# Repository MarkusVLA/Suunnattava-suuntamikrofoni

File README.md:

# Suunnattava suuntamikrofoni 

Suunnattava suuntamikrofoni on laite, jolla voidaan elektronisesti ohjata äänityksen suuntaa käännettävän suuntauksen avulla. Laite koostuu kahdesta piirikortista: Ensimmäinen piirikortti sisältää kuuden mikrofonin ryhmän, josta luetaan dataa. Toinen piirikortti hoitaa signaalinkäsittelyn ja laitteen ohjauksen ESP32-S3-mikro-ohjaimeen perustuvalla järjestelmällä.

## Mikrofonipiiri

-   ...

## Signaalinkäsittelypiiri

<p float="left">

  <p>Kuva 1: ESP32-DSP piirikaavio ja piirikortti</p>
</p>

<p float="left">
  
  <p>Kuva 2: ESP32-DSP piirikortti toteutettuna</p>
</p>

## TODO
* [x] DSP alustan suunnittelu
* [x] Mikrofoonipiirin suunnittelu
* [x] Piirikorttien kasaus
* [x] Datan keräys ADS8688-ADC:n avulla
* [ ] Beam forming algoritmi
* [ ] Äänen toisto käyttäjälle

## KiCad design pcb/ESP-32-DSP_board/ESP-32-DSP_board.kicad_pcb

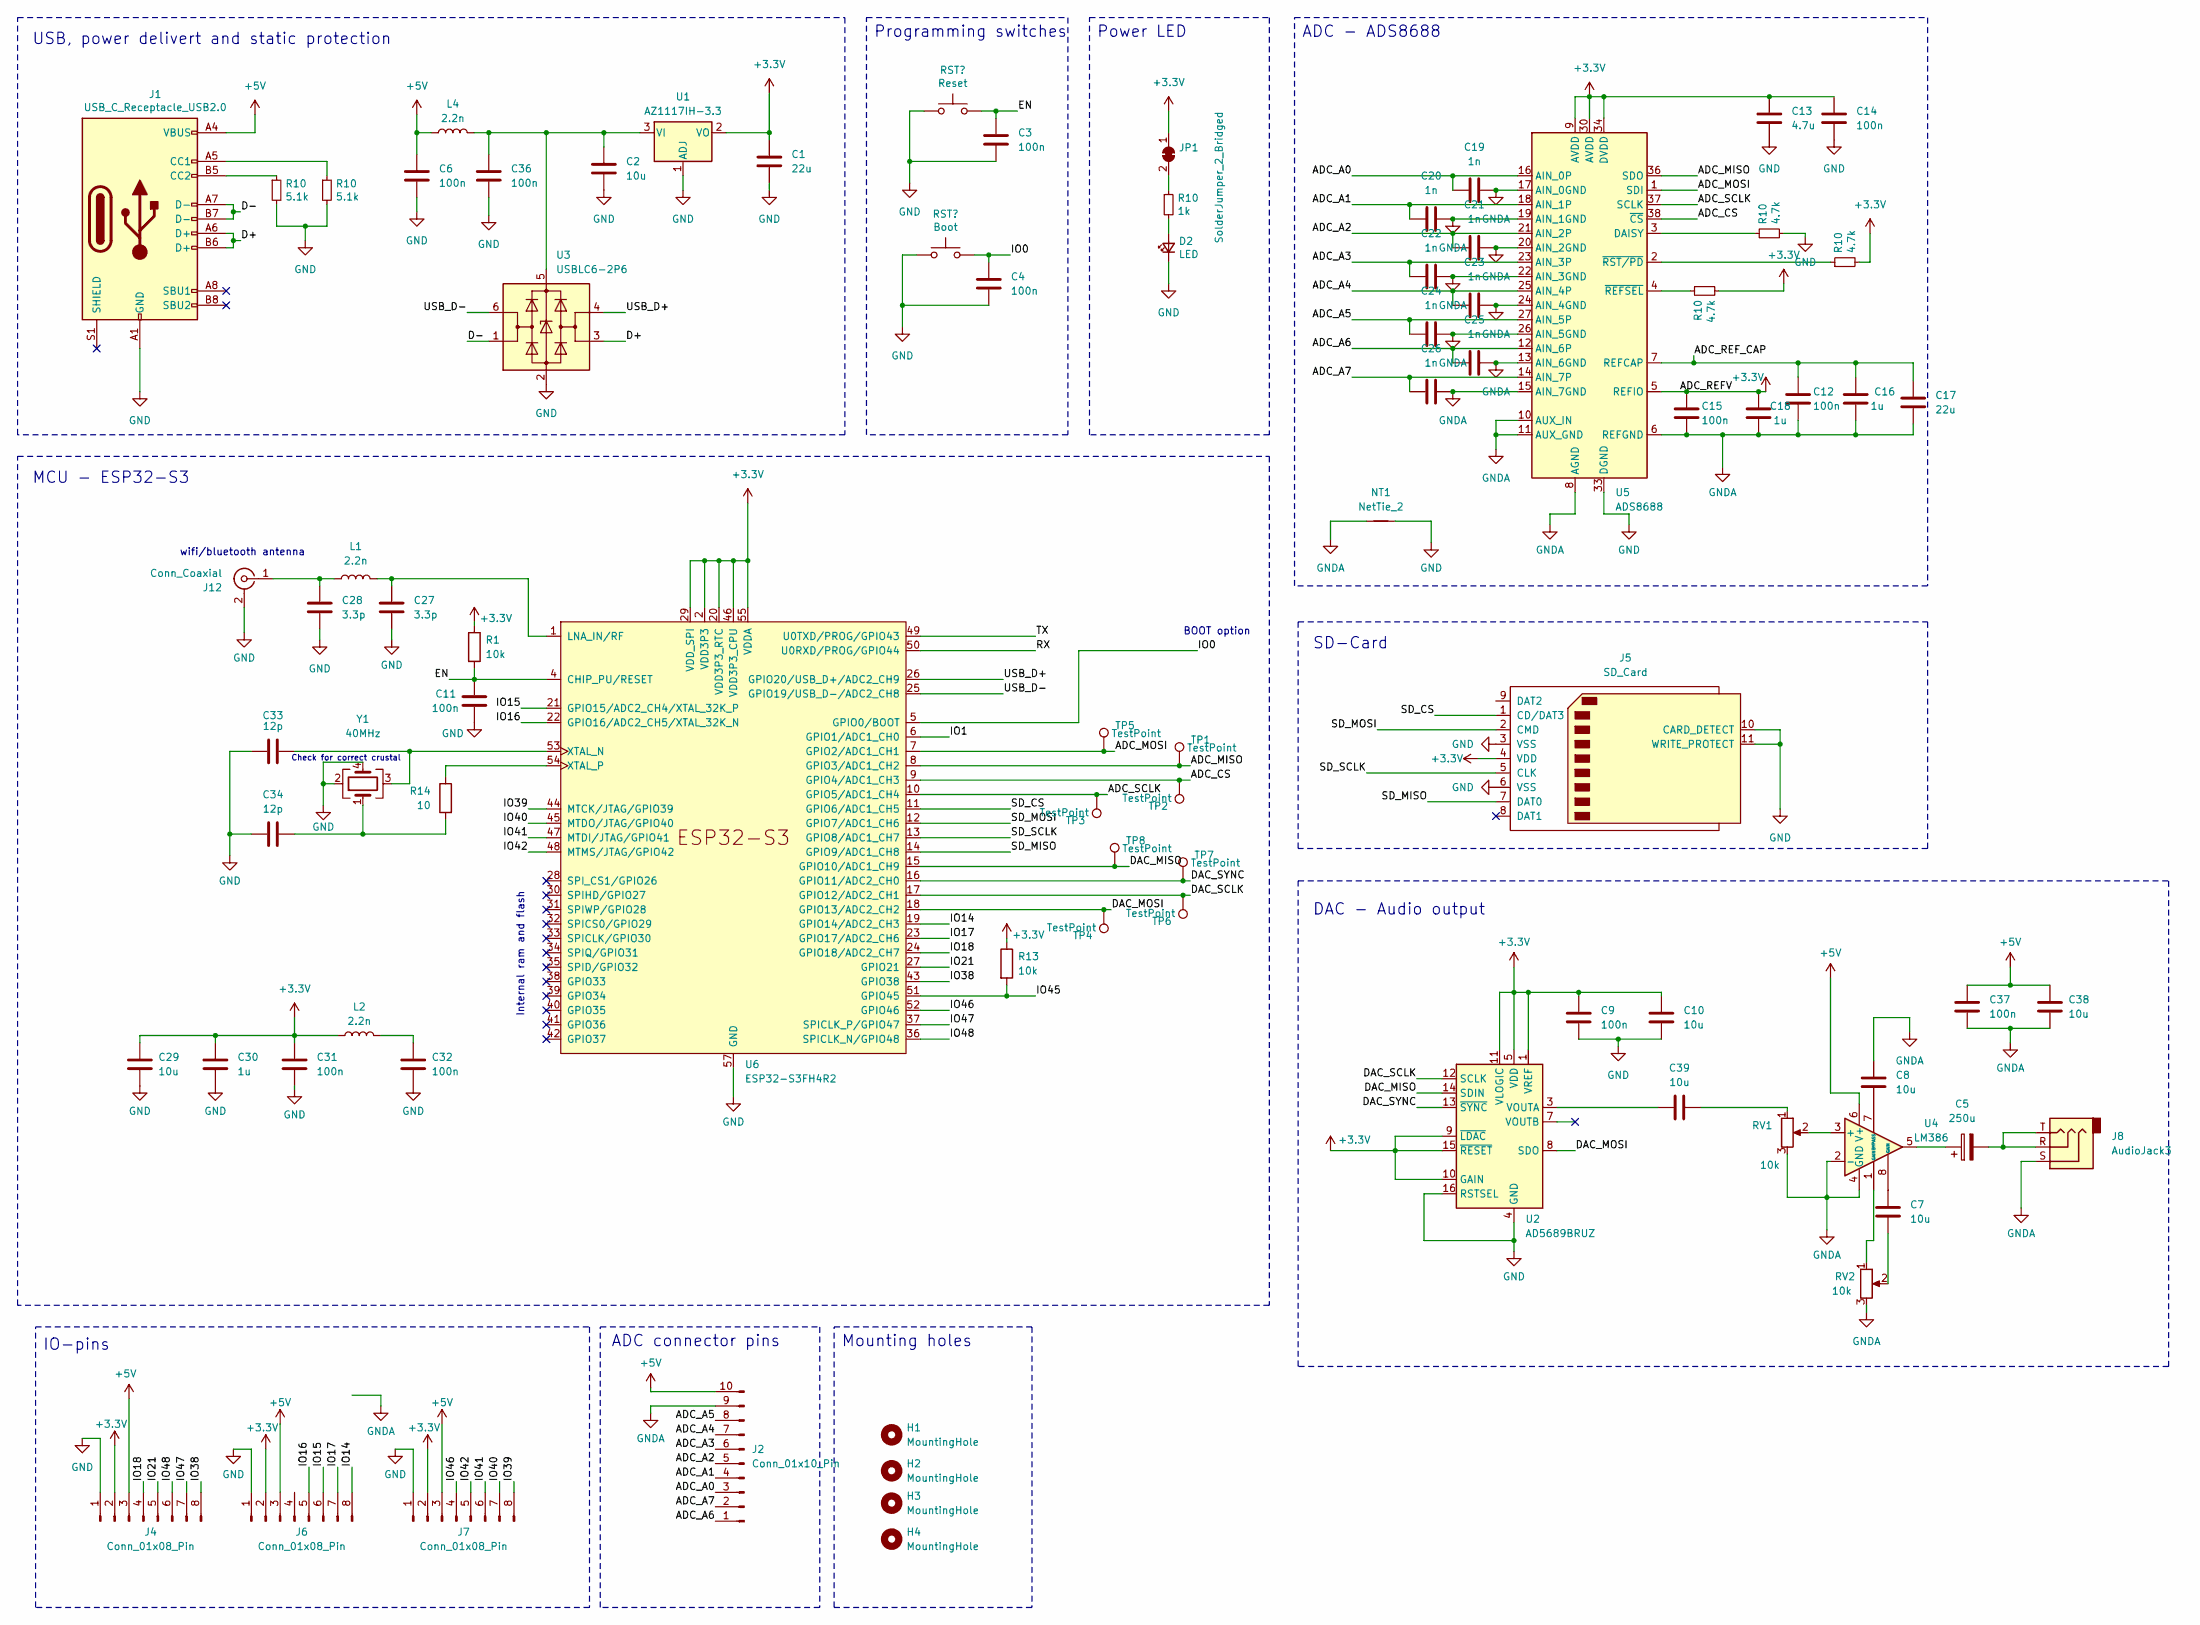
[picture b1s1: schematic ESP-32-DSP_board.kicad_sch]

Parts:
C1, C17: 22u; C_0805_2012Metric
C2, C7, C8, C10, C29, C38, C39: 10u; C_0603_1608Metric
C3, C4, C6, C9, C11, C12, C14, C15, C31, C32, C36, C37: 100n; C_0402_1005Metric
C5: 250u; CP_Radial_D5.0mm_P2.50mm
C13: 4.7u; C_0603_1608Metric
C16, C18, C30: 1u; C_0603_1608Metric
C19, C20, C21, C22, C23, C24, C25, C26: 1n; C_0402_1005Metric
C27, C28: 3.3p; C_0402_1005Metric
C33, C34: 12p; C_0402_1005Metric
D2: LED; LED_0805_2012Metric_Pad1.15x1.40mm_HandSolder; LCSC C205445
H1, H2, H3, H4: MountingHole; MountingHole_2.2mm_M2_DIN965_Pad
J1: USB_C_Receptacle_USB2.0; USB_C_Receptacle_G-Switch_GT-USB-7010ASV
J2: Conn_01x10_Pin; PinHeader_1x10_P2.54mm_Vertical
J4, J6, J7: Conn_01x08_Pin; PinHeader_1x08_P2.54mm_Vertical
J5: SD_Card; microSD_HC_Hirose_DM3D-SF
J8: AudioJack3; Jack_3.5mm_CUI_SJ-3523-SMT_Horizontal
J12: Conn_Coaxial; Texas_SWRA117D_2.4GHz_Right
JP1: SolderJumper_2_Bridged; SolderJumper-2_P1.3mm_Bridged_RoundedPad1.0x1.5mm
L1, L2, L4: 2.2n; L_0603_1608Metric
NT1: NetTie_2; NetTie-2_THT_Pad1.0mm
R1, R13: 10k; R_0402_1005Metric
R10: 4.7k; R_0402_1005Metric; LCSC C163928
R14: 10; R_0805_2012Metric
RV1, RV2: 10k; Potentiometer_Bourns_3214J_Horizontal
SW1: Reset; SW_Push_SPST_NO_Alps_SKRK; LCSC C115357
TP1, TP2, TP3, TP4, TP5, TP6, TP7, TP8: TestPoint; TestPoint_Pad_D1.0mm
U1: AZ1117IH-3.3; SOT-223-3_TabPin2
U2: AD5689BRUZ; TSSOP-16_4.4x5mm_P0.65mm
U3: USBLC6-2P6; SOT-666
U4: LM386; SOIC-8_3.9x4.9mm_P1.27mm
U5: ADS8688; TSSOP-38_4.4x9.7mm_P0.5mm; JLCPCB Rotation Offset -90
U6: ESP32-S3FH4R2; QFN-56-1EP_7x7mm_P0.4mm_EP5.6x5.6mm
Y1: 40MHz; Crystal_SMD_3225-4Pin_3.2x2.5mm

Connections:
+3.3V: C1.1, C9.1, C10.1, C13.1, C14.1, C15.2, C18.1, C29.1, C30.1, C31.1, J4.2, J5.4 (VDD), J6.2, J7.2, JP1.1 (A), L2.1, R1.1, R13.1, U1.2 (VO), U2.1 (VREF), U2.5 (VDD), U2.9 (~LDAC), U2.10 (GAIN), U2.11 (VLOGIC), U2.15 (~RESET), U5.5 (REFIO), U5.9 (AVDD), U5.30 (AVDD), U5.34 (DVDD), U6.2 (VDD3P3), U6.3 (VDD3P3), U6.20 (VDD3P3_RTC), U6.29 (VDD_SPI), U6.46 (VDD3P3_CPU), U6.55 (VDDA), U6.56 (VDDA); also elsewhere on the board
+5V: C6.1, C37.1, C38.1, J1.A4 (VBUS), J1.A9 (VBUS), J1.B4 (VBUS), J1.B9 (VBUS), J2.10, J4.3, J6.3, J7.3, L4.1, U4.6 (V+)
/ADC_A0: C19.1, J2.3, U5.16 (AIN_0P)
/ADC_A1: C20.1, J2.4, U5.18 (AIN_1P)
/ADC_A2: C21.2, J2.5, U5.21 (AIN_2P)
/ADC_A3: C22.2, J2.6, U5.23 (AIN_3P)
/ADC_A4: C23.2, J2.7, U5.25 (AIN_4P)
/ADC_A5: C24.2, J2.8, U5.27 (AIN_5P)
/ADC_A6: C25.1, J2.1, U5.12 (AIN_6P)
/ADC_A7: C26.2, J2.2, U5.14 (AIN_7P)
/ADC_CS: TP2.1, U5.38 (~CS), U6.9 (GPIO4/ADC1_CH3)
/ADC_MISO: TP1.1, U5.36 (SDO), U6.8 (GPIO3/ADC1_CH2)
/ADC_MOSI: TP5.1, U5.1 (SDI), U6.7 (GPIO2/ADC1_CH1)
/ADC_REF_CAP: C12.2, C16.1, C17.1, U5.7 (REFCAP)
/ADC_SCLK: TP3.1, U5.37 (SCLK), U6.10 (GPIO5/ADC1_CH4)
/D+: J1.A6 (D+), J1.B6 (D+), U3.3 (I/O2)
/D-: J1.A7 (D-), J1.B7 (D-), U3.1 (I/O1)
/DAC_MISO: TP8.1, U2.14 (SDIN), U6.15 (GPIO10/ADC1_CH9)
/DAC_MOSI: TP4.1, U2.8 (SDO), U6.18 (GPIO13/ADC2_CH2)
/DAC_SCLK: TP6.1, U2.12 (SCLK), U6.17 (GPIO12/ADC2_CH1)
/DAC_SYNC: TP7.1, U2.13 (~SYNC), U6.16 (GPIO11/ADC2_CH0)
/IO1: U6.6 (GPIO1/ADC1_CH0)
/IO14: J6.8, U6.19 (GPIO14/ADC2_CH3)
/IO15: J6.6, U6.21 (GPIO15/ADC2_CH4/XTAL_32K_P)
/IO16: J6.5, U6.22 (GPIO16/ADC2_CH5/XTAL_32K_N)
/IO17: J6.7, U6.23 (GPIO17/ADC2_CH6)
/IO18: J4.4, U6.24 (GPIO18/ADC2_CH7)
/IO21: J4.5, U6.27 (GPIO21)
/IO38: J4.8, U6.43 (GPIO38)
/IO39: J7.8, U6.44 (MTCK/JTAG/GPIO39)
/IO40: J7.7, U6.45 (MTDO/JTAG/GPIO40)
/IO41: J7.6, U6.47 (MTDI/JTAG/GPIO41)
/IO42: J7.5, U6.48 (MTMS/JTAG/GPIO42)
/IO45: R13.2, U6.51 (GPIO45)
/IO46: J7.4, U6.52 (GPIO46)
/IO47: J4.7, U6.37 (SPICLK_P/GPIO47)
/IO48: J4.6, U6.36 (SPICLK_N/GPIO48)
/RX: U6.50 (U0RXD/PROG/GPIO44)
/SD_CS: J5.1 (CD/DAT3), U6.11 (GPIO6/ADC1_CH5)
/SD_MISO: J5.7 (DAT0), U6.14 (GPIO9/ADC1_CH8)
/SD_MOSI: J5.2 (CMD), U6.12 (GPIO7/ADC1_CH6)
/SD_SCLK: J5.5 (CLK), U6.13 (GPIO8/ADC1_CH7)
/TX: U6.49 (U0TXD/PROG/GPIO43)
/USB_D+: U3.4 (I/O2), U6.26 (GPIO20/USB_D+/ADC2_CH9)
/USB_D-: U3.6 (I/O1), U6.25 (GPIO19/USB_D-/ADC2_CH8)
GND: C1.2, C2.2, C3.2, C4.2, C6.2, C9.2, C10.2, C11.2, C13.2, C14.2, C27.2, C28.2, C29.2, C30.2, C31.2, C32.2, C33.1, C34.1, C36.2, J1.A1 (GND), J1.A12 (GND), J1.B1 (GND), J1.B12 (GND), J4.1, J5.3 (VSS), J5.6 (VSS), J5.10 (CARD_DETECT), J5.11 (WRITE_PROTECT), J6.1, J7.1, J12.2 (Ext), NT1.2, SW1.2, U1.1 (ADJ), U2.4 (GND), U2.16 (RSTSEL), U3.2 (GND), U5.33 (DGND), U6.57 (GND), Y1.2, Y1.4; also elsewhere on the board
GNDA: C8.1, C12.1, C15.1, C16.2, C17.2, C18.2, C19.2, C20.2, C21.1, C22.1, C23.1, C24.1, C25.2, C26.1, C37.2, C38.2, J2.9, J8.S, NT1.1, RV1.3, RV2.3, U4.2 (-), U4.4 (GND), U5.6 (REFGND), U5.8 (AGND), U5.10 (AUX_IN), U5.11 (AUX_GND), U5.13 (AIN_6GND), U5.15 (AIN_7GND), U5.17 (AIN_0GND), U5.19 (AIN_1GND), U5.20 (AIN_2GND), U5.22 (AIN_3GND), U5.24 (AIN_4GND), U5.26 (AIN_5GND), U5.28 (AGND), U5.29 (AGND), U5.31 (AGND), U5.32 (AGND)
unnamed: C5.1, U4.5
unnamed: C5.2, J8.R, J8.T
unnamed: C7.1, U4.8 (GAIN)
unnamed: C7.2, RV2.2
unnamed: C32.1, L2.2
unnamed: C34.2, R14.2, Y1.1
unnamed: C39.2, RV1.1
unnamed 55: J1.A5 (CC1); also elsewhere on the board
unnamed 56: J1.B5 (CC2); also elsewhere on the board
unnamed: C28.1, J12.1 (In), L1.1
unnamed 58: JP1.2 (B); also elsewhere on the board
unnamed: RV2.1, U4.1 (GAIN)
unnamed: C2.1, C36.1, L4.2, U1.3 (VI), U3.5 (VBUS)
unnamed: C39.1, U2.3 (VOUTA)
unnamed: RV1.2, U4.3 (+)
unnamed: C8.2, U4.7 (BYPASS)
unnamed 64: U5.3 (DAISY); also elsewhere on the board
unnamed 65: U5.4 (~REFSEL); also elsewhere on the board
unnamed 66: U5.2 (~RST/PD); also elsewhere on the board
unnamed: C27.1, L1.2, U6.1 (LNA_IN/RF)
unnamed: C33.2, U6.53 (XTAL_N), Y1.3
unnamed: R14.1, U6.54 (XTAL_P)

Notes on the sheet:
MCU - ESP32-S3
wifi/bluetooth antenna
USB, power delivert and static protection
Power LED
IO-pins
Internal ram and flash
ADC connector pins
BOOT option
Check for correct crustal
DAC - Audio output
ADC - ADS8688
Programming switches
Mounting holes
SD-Card

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
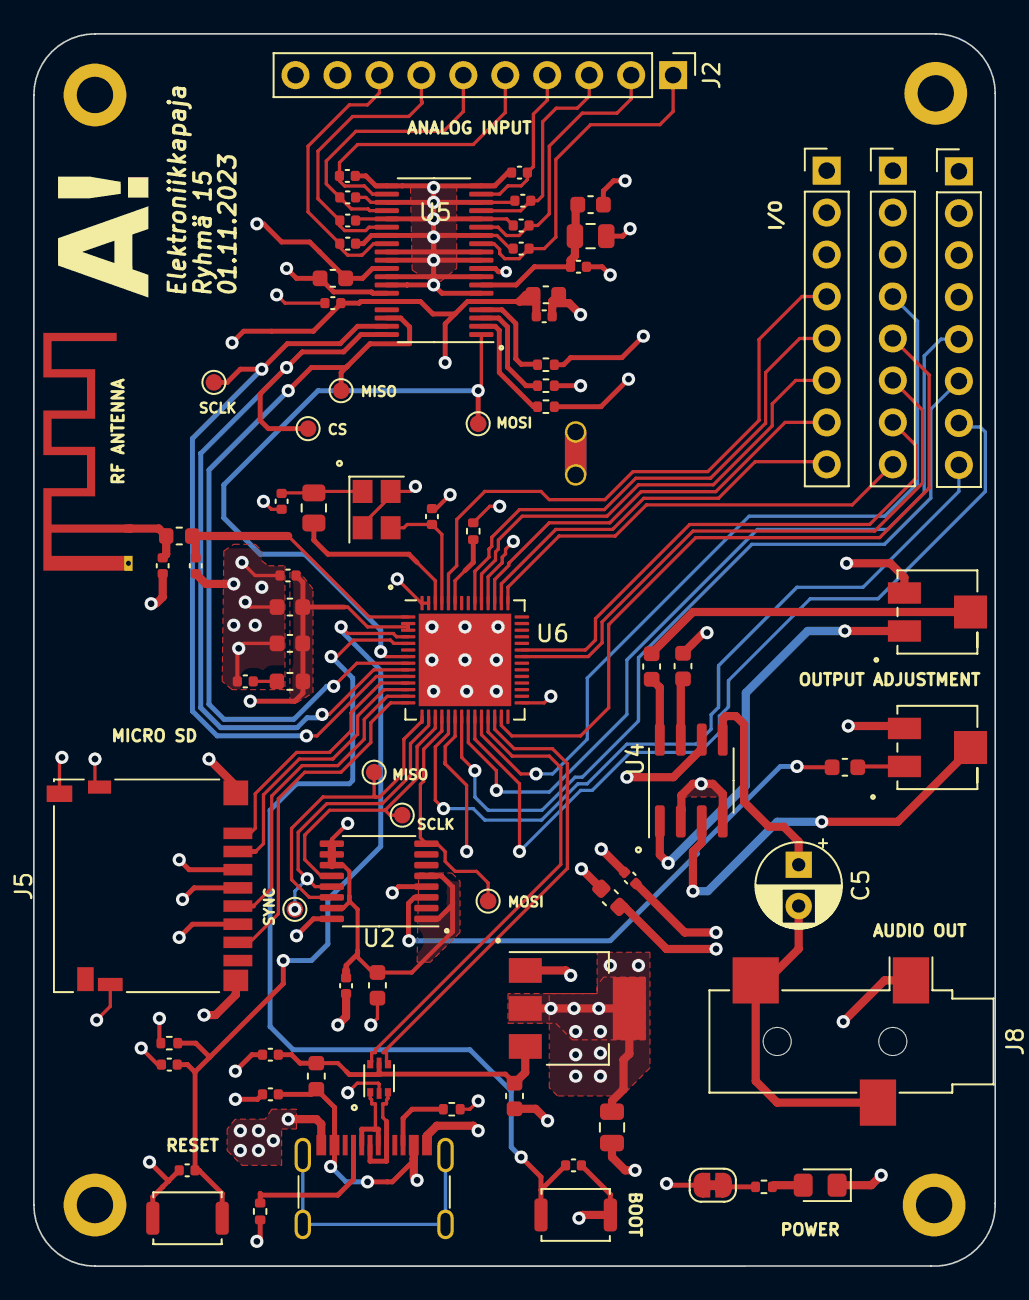
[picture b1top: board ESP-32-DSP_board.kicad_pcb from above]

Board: 4 copper layers, 58.2 x 74.6 mm, 84 parts (0 on the bottom side), 69 nets.

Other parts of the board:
D1: LED; LED_0805_2012Metric_Pad1.15x1.40mm_HandSolder
R3: 1k; R_0402_1005Metric
R5, R8, R9: 4.7k; R_0402_1005Metric
R6, R7: 5.1k; R_0402_1005Metric
SW2: Boot; SW_Push_SPST_NO_Alps_SKRK

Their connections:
+3.3V: R5.2, R8.2; also elsewhere on the board
GND: D1.1 (K), R6.2, R7.2, R9.2, SW2.2; also elsewhere on the board
unnamed: D1.2 (A), R3.2
unnamed 55: R7.1; also elsewhere on the board
unnamed 56: R6.1; also elsewhere on the board
unnamed 58: R3.1; also elsewhere on the board
unnamed 64: R9.1; also elsewhere on the board
unnamed 65: R8.1; also elsewhere on the board
unnamed 66: R5.1; also elsewhere on the board

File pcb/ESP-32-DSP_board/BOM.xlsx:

Designator | Footprint | Quantity | Value | LCSC Part # | Tilaus määrä
C1 | 402 | 1 | 22u
C10, C2, C29, C7, C8 | 603 | 5 | 10u
C12, C14, C15, C3, C31, C32, C36, C4, C6 | 402 | 9 | 100n
C13 | 603 | 1 | 4.7u
C16, C18, C30 | 603 | 3 | 1u
C17 | 805 | 1 | 22u
C19, C20, C21, C22, C23, C24, C25, C26 | 402 | 8 | 1n
C27, C28 | 402 | 2 | 3.3p
C33, C34 | 402 | 2 | 12p
C5 | CP_Radial_D5.0mm_P2.50mm | 1 | 250u
C9 | 603 | 1 | 100n
D1 | 805 | 1 | LED
H1, H2, H3, H4 | MountingHole_2.2mm_M2_DIN965_Pad | 4 | MountingHole
J1 | USB_C_Receptacle_G-Switch_GT-USB-7010ASV | 1 | USB_C_Receptacle_USB2.0
J12 | U.FL_Hirose_U.FL-R-SMT-1_Vertical | 1 | Conn_Coaxial
J2 | PinHeader_1x10_P2.54mm_Vertical | 1 | Conn_01x10_Pin
J3 | Jack_3.5mm_CUI_SJ-3523-SMT_Horizontal | 1 | AudioJack2_Ground
J4, J6, J7 | PinHeader_1x08_P2.54mm_Vertical | 3 | Conn_01x08_Pin
J5 | microSD_HC_Hirose_DM3D-SF | 1 | SD_Card
JP1 | SolderJumper-2_P1.3mm_Bridged_RoundedPad1.0x1.5mm | 1 | SolderJumper_2_Bridged
L1, L2, L4 | 603 | 3 | 2.2n
R13 | 402 | 1 | 10k
R14 | 805 | 1 | 10
R3 | 402 | 1 | 1k
R5, R8, R9 | 402 | 3 | 4.7k
R6, R7 | 402 | 2 | 5.1k
RV1, RV2 | Potentiometer_ACP_CA6-VSMD_Vertical | 2 | R_Potentiometer
SW1 | SW_Push_SPST_NO_Alps_SKRK | 1 | Reset
SW2 | SW_Push_SPST_NO_Alps_SKRK | 1 | Boot
U1 | SOT-223-3_TabPin2 | 1 | AZ1117IH-3.3
U2 | TSSOP-16_4.4x5mm_P0.65mm | 1 | AD5689BRUZ
U3 | SOT-666 | 1 | USBLC6-2P6
U4 | SOIC-8_3.9x4.9mm_P1.27mm | 1 | LM386
U5 | TSSOP-38_4.4x9.7mm_P0.5mm | 1 | ADS8688
U6 | QFN-56-1EP_7x7mm_P0.4mm_EP5.6x5.6mm | 1 | ESP32-S3FH4R2
Y1 | Crystal_SMD_3225-4Pin_3.2x2.5mm | 1 | 40MHz

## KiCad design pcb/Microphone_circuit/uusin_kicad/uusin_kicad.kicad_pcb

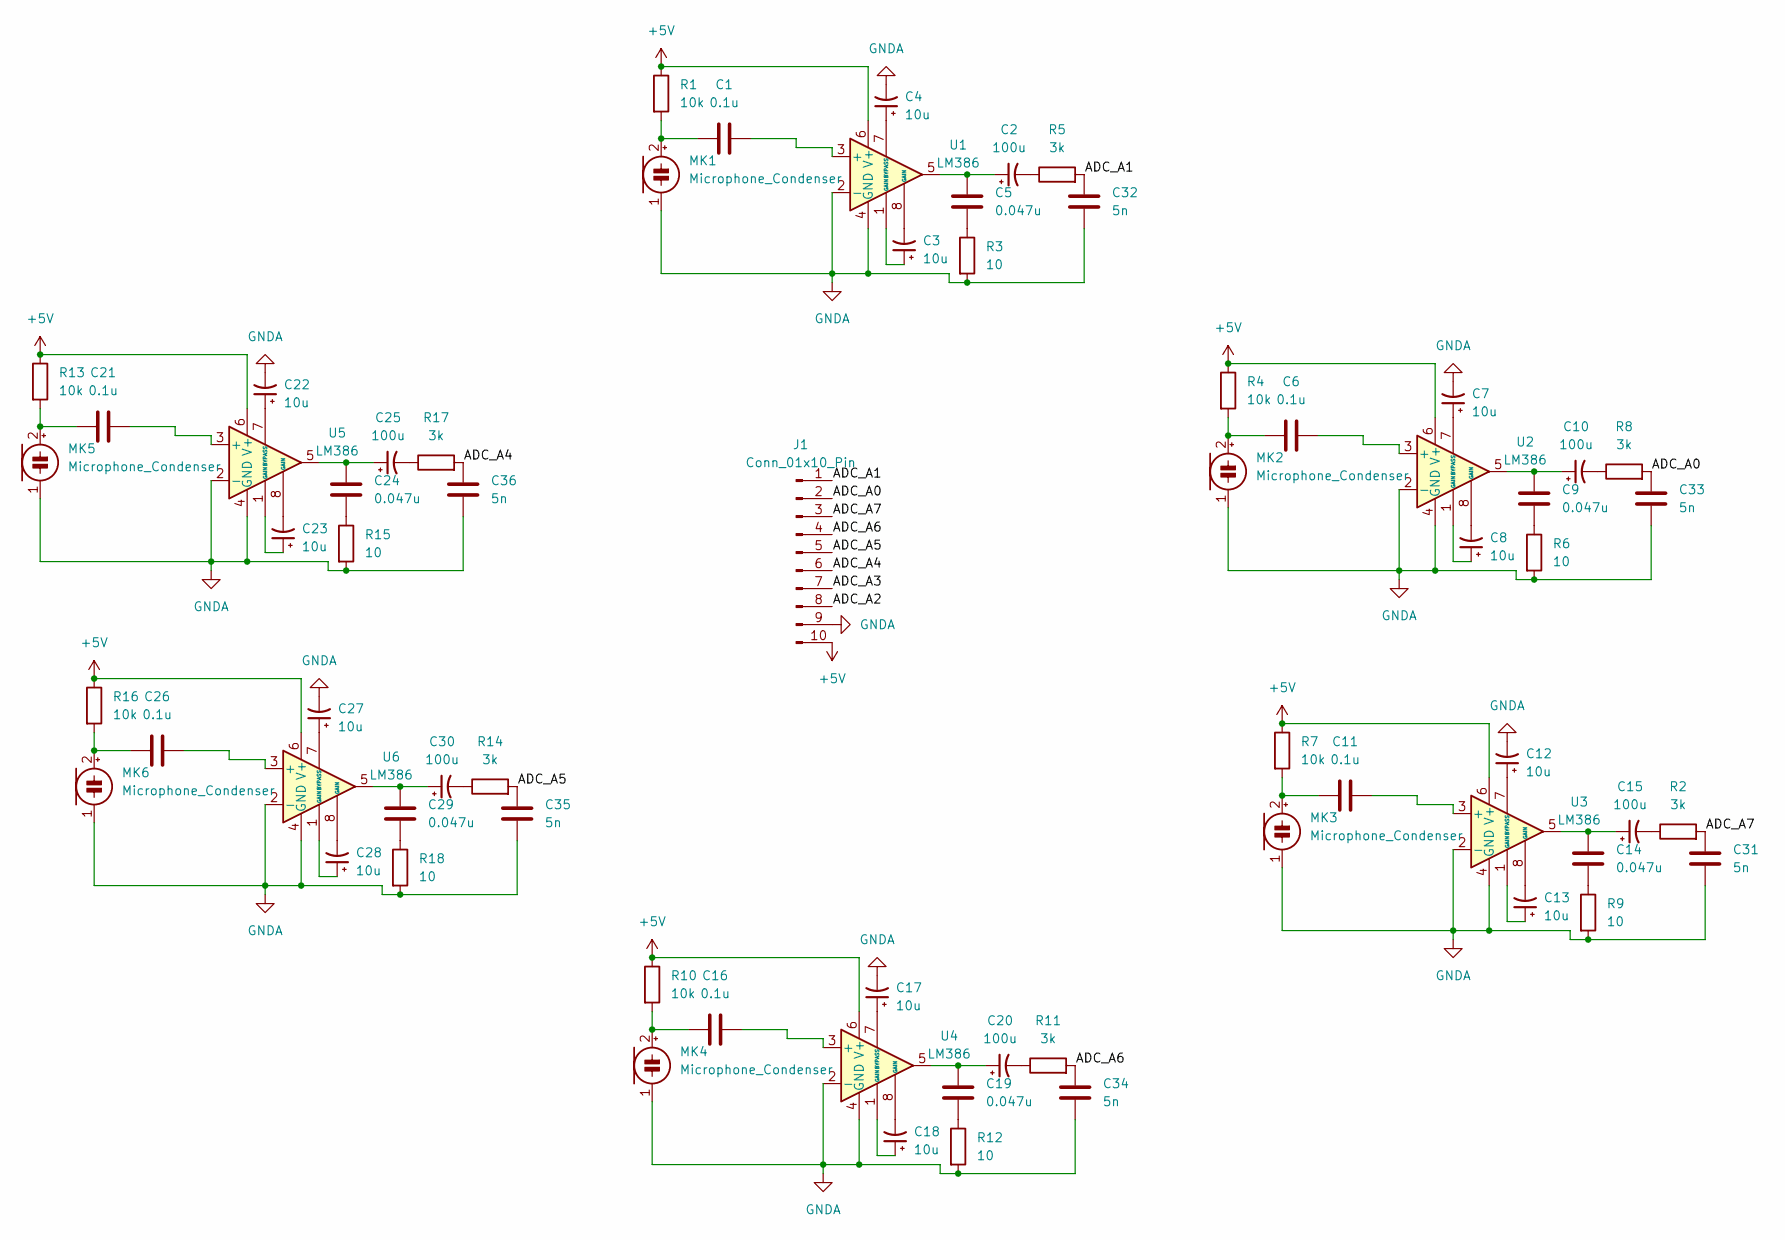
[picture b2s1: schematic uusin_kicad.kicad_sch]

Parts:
C1, C6, C11, C16, C21, C26: 0.1u; C_0805_2012Metric_Pad1.18x1.45mm_HandSolder
C2, C10, C15, C20, C25, C30: 100u; CP_Radial_D7.5mm_P2.50mm
C3, C4, C7, C8, C12, C13, C17, C18, C22, C23, C27, C28: 10u; C_0805_2012Metric_Pad1.18x1.45mm_HandSolder
C5, C9, C14, C19, C24, C29: 0.047u; C_0805_2012Metric_Pad1.18x1.45mm_HandSolder
C31, C32, C33, C34, C35, C36: 5n; C_0805_2012Metric_Pad1.18x1.45mm_HandSolder
J1: Conn_01x10_Pin; PinSocket_1x10_P2.54mm_Vertical
MK1, MK2, MK3, MK4, MK5, MK6: Microphone_Condenser; Mikrophoni1
R1, R4, R7, R10, R13, R16: 10k; R_0805_2012Metric_Pad1.20x1.40mm_HandSolder
R2, R5, R8, R11, R14, R17: 3k; R_0805_2012Metric_Pad1.20x1.40mm_HandSolder
R3, R6, R9, R12, R15, R18: 10; R_0805_2012Metric_Pad1.20x1.40mm_HandSolder
U1, U2, U3, U4, U5, U6: LM386; DIP-8_W7.62mm

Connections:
+5V: J1.10, R1.1, R4.1, R7.1, R10.1, R13.1, R16.1, U1.6 (V+), U2.6 (V+), U3.6 (V+), U4.6 (V+), U5.6 (V+), U6.6 (V+)
/ADC_A0: C33.1, J1.2, R8.2
/ADC_A1: C32.1, J1.1, R5.2
/ADC_A2: J1.8
/ADC_A3: J1.7
/ADC_A4: C36.1, J1.6, R17.2
/ADC_A5: C35.1, J1.5, R14.2
/ADC_A6: C34.1, J1.4, R11.2
/ADC_A7: C31.1, J1.3, R2.2
GNDA: C4.2, C7.2, C12.2, C17.2, C22.2, C27.2, C31.2, C32.2, C33.2, C34.2, C35.2, C36.2, J1.9, MK1.1 (-), MK2.1 (-), MK3.1 (-), MK4.1 (-), MK5.1 (-), MK6.1 (-), R3.2, R6.2, R9.2, R12.2, R15.2, R18.2, U1.2 (-), U1.4 (GND), U2.2 (-), U2.4 (GND), U3.2 (-), U3.4 (GND), U4.2 (-), U4.4 (GND), U5.2 (-), U5.4 (GND), U6.2 (-), U6.4 (GND)
unnamed: C2.1, C5.1, U1.5
unnamed: C2.2, R5.1
unnamed: C3.1, U1.1 (GAIN)
unnamed: C3.2, U1.8 (GAIN)
unnamed: C5.2, R3.1
unnamed: C8.1, U2.1 (GAIN)
unnamed: C8.2, U2.8 (GAIN)
unnamed: C9.2, R6.1
unnamed: C9.1, C10.1, U2.5
unnamed: C10.2, R8.1
unnamed: C13.1, U3.1 (GAIN)
unnamed: C13.2, U3.8 (GAIN)
unnamed: C14.1, C15.1, U3.5
unnamed: C14.2, R9.1
unnamed: C15.2, R2.1
unnamed: C18.1, U4.1 (GAIN)
unnamed: C18.2, U4.8 (GAIN)
unnamed: C19.1, C20.1, U4.5
unnamed: C19.2, R12.1
unnamed: C20.2, R11.1
unnamed: C23.1, U5.1 (GAIN)
unnamed: C23.2, U5.8 (GAIN)
unnamed: C24.1, C25.1, U5.5
unnamed: C24.2, R15.1
unnamed: C25.2, R17.1
unnamed: C28.1, U6.1 (GAIN)
unnamed: C28.2, U6.8 (GAIN)
unnamed: C29.1, C30.1, U6.5
unnamed: C29.2, R18.1
unnamed: C30.2, R14.1
unnamed: C1.1, MK1.2 (+), R1.2
unnamed: C6.1, MK2.2 (+), R4.2
unnamed: C11.1, MK3.2 (+), R7.2
unnamed: C16.1, MK4.2 (+), R10.2
unnamed: C21.1, MK5.2 (+), R13.2
unnamed: C26.1, MK6.2 (+), R16.2
unnamed: C1.2, U1.3 (+)
unnamed: C4.1, U1.7 (BYPASS)
unnamed: C6.2, U2.3 (+)
unnamed: C7.1, U2.7 (BYPASS)
unnamed: C11.2, U3.3 (+)
unnamed: C12.1, U3.7 (BYPASS)
unnamed: C16.2, U4.3 (+)
unnamed: C17.1, U4.7 (BYPASS)
unnamed: C21.2, U5.3 (+)
unnamed: C22.1, U5.7 (BYPASS)
unnamed: C26.2, U6.3 (+)
unnamed: C27.1, U6.7 (BYPASS)

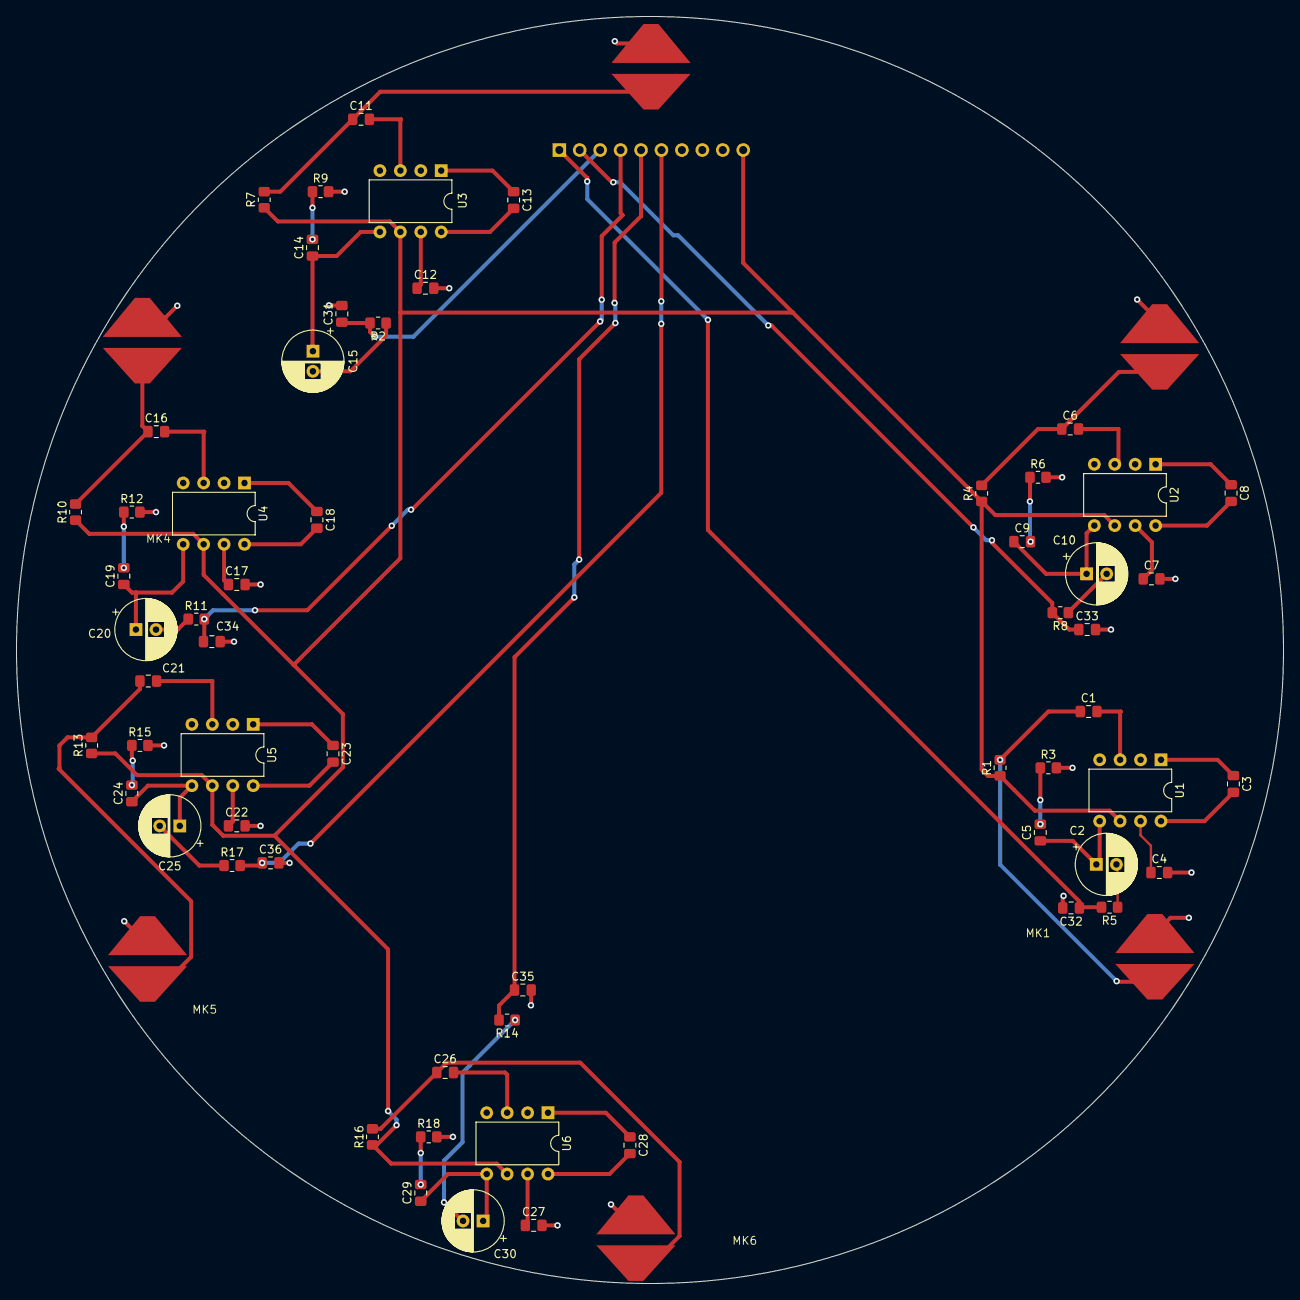
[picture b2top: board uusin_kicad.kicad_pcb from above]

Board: 2 copper layers, 157.5 x 157.5 mm, 67 parts (1 on the bottom side), 56 nets.

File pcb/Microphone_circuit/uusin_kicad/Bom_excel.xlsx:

Designator | Footprint | Tilausmäärä | Value | LCSC Part #
C1, C11, C16, C21, C26, C6 | 805 | 8 | 0.1u | https://www.digikey.fi/fi/products/detail/kemet/C0805C104M5R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
C10, C15, C2, C20, C25, C30 | CP_Radial_D7.5mm_P2.50mm |  | 100u | pajalta?
C12, C13, C17, C18, C22, C23, C27, C28, C3, C4, C7, C8 | 805 | 14 | 10u | https://www.digikey.fi/fi/products/detail/murata-electronics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
C14, C19, C24, C29, C5, C9 | 805 | 8 | 0.047u | https://www.digikey.fi/fi/products/detail/kemet/C0805C473K5R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
C31, C32, C33, C34, C35, C36 | 805 | 8 | 5n | https://www.digikey.fi/fi/products/detail/kyocera-avx/08055C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
MK1, MK2, MK3, MK4, MK5, MK6 | Mikrophoni1 | 8 | Microphone_Condenser | https://www.digikey.fi/fi/products/detail/ole-wolff-electron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
R1, R10, R13, R16, R4, R7 | 805 | 8 | 10k | https://www.digikey.fi/fi/products/detail/stackpole-electron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
R11, R14, R17, R2, R5, R8 | 805 | 8 | 3k | https://www.digikey.fi/fi/products/detail/stackpole-electron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
R12, R15, R18, R3, R6, R9 | 805 | 8 | 10 | https://www.digikey.fi/fi/products/detail/panasonic-electron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
U1, U2, U3, U4, U5, U6 | DIP-8_W7.62mm | 8 | LM386 | https://www.digikey.fi/fi/products/detail/texas-instruments/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

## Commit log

2023-09-18 new file: .gitignore, modified: README.md
2023-09-19 Added pcb proto
2023-09-19 esp-32 dev module test code
2023-09-19 Separated GND and GNDA
2023-09-20 Updated ADC configutation
2023-09-20 Arduino framework test code for MCP3008
2023-09-20 Added hardware timer to control ADC sample rate
2023-09-21 removed old ESP-idf code. Added serial reading tool.
2023-09-21 Updated .gitignore
2023-09-21 Latest pcb version
2023-09-26 Changed from dev module to ESP-dsp module.
2023-09-26 Organised code and added hardware timer to ADS8688 class =)
2023-09-27 Added playback queue
2023-09-27 Added muti-channel support to ADC and created dedicated buffer class
2023-09-27 Modified README.md
2023-10-25 tein testi tiedoston
2023-10-27 Removed test file
2023-10-27 tein low pass 20kHz simulaation
2023-10-27 Add new directory
2023-10-27 ESP32-S3 version of dsp board with SD-card and DAC added
2023-10-27 latest firmware version
2023-10-29 First working version of S3 dsp board
2023-11-01 Test file
2023-11-01 testi
2023-11-01 removed testi.txt
2023-11-01 Removed folders
2023-11-01 vihdoin äijät
2023-11-01 ESP32-S3 DSP updates
2023-11-02 Fixed mistake in S3 dsp
2023-11-02 ESP32-S3 DSP board
2023-11-04 Componets list for S3 dsp board
2023-11-04 Added all component order links
2023-11-04 Added local pcb modifications
2023-11-04 Removed KiCad autosave files
2023-11-04 Added board production files
2023-11-04 ESP32 DSP board Gerber files
2023-11-04 Added price to components lists
2023-11-04 Added production files for microphone circuit
2023-11-07 Digikey and Mouser order forms
2023-11-13 Removed order forms from git
2023-11-13 cleanded pcb directory
2023-11-14 Updated microcontroller model in platformio and added SerialStreamBuf class
2023-11-16 Added Task manager and improved serial communication
2023-11-24 beamforming algorithm
2023-11-27 Updated firmware tasks and added a few images.
2023-11-27 Added images
2023-11-27 added new image to README
2023-12-30 ADS 8688 measurement code and beam forming simulation
